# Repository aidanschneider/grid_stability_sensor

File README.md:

# grid_stability_sensor
Custom grid stability analyzer PCB.

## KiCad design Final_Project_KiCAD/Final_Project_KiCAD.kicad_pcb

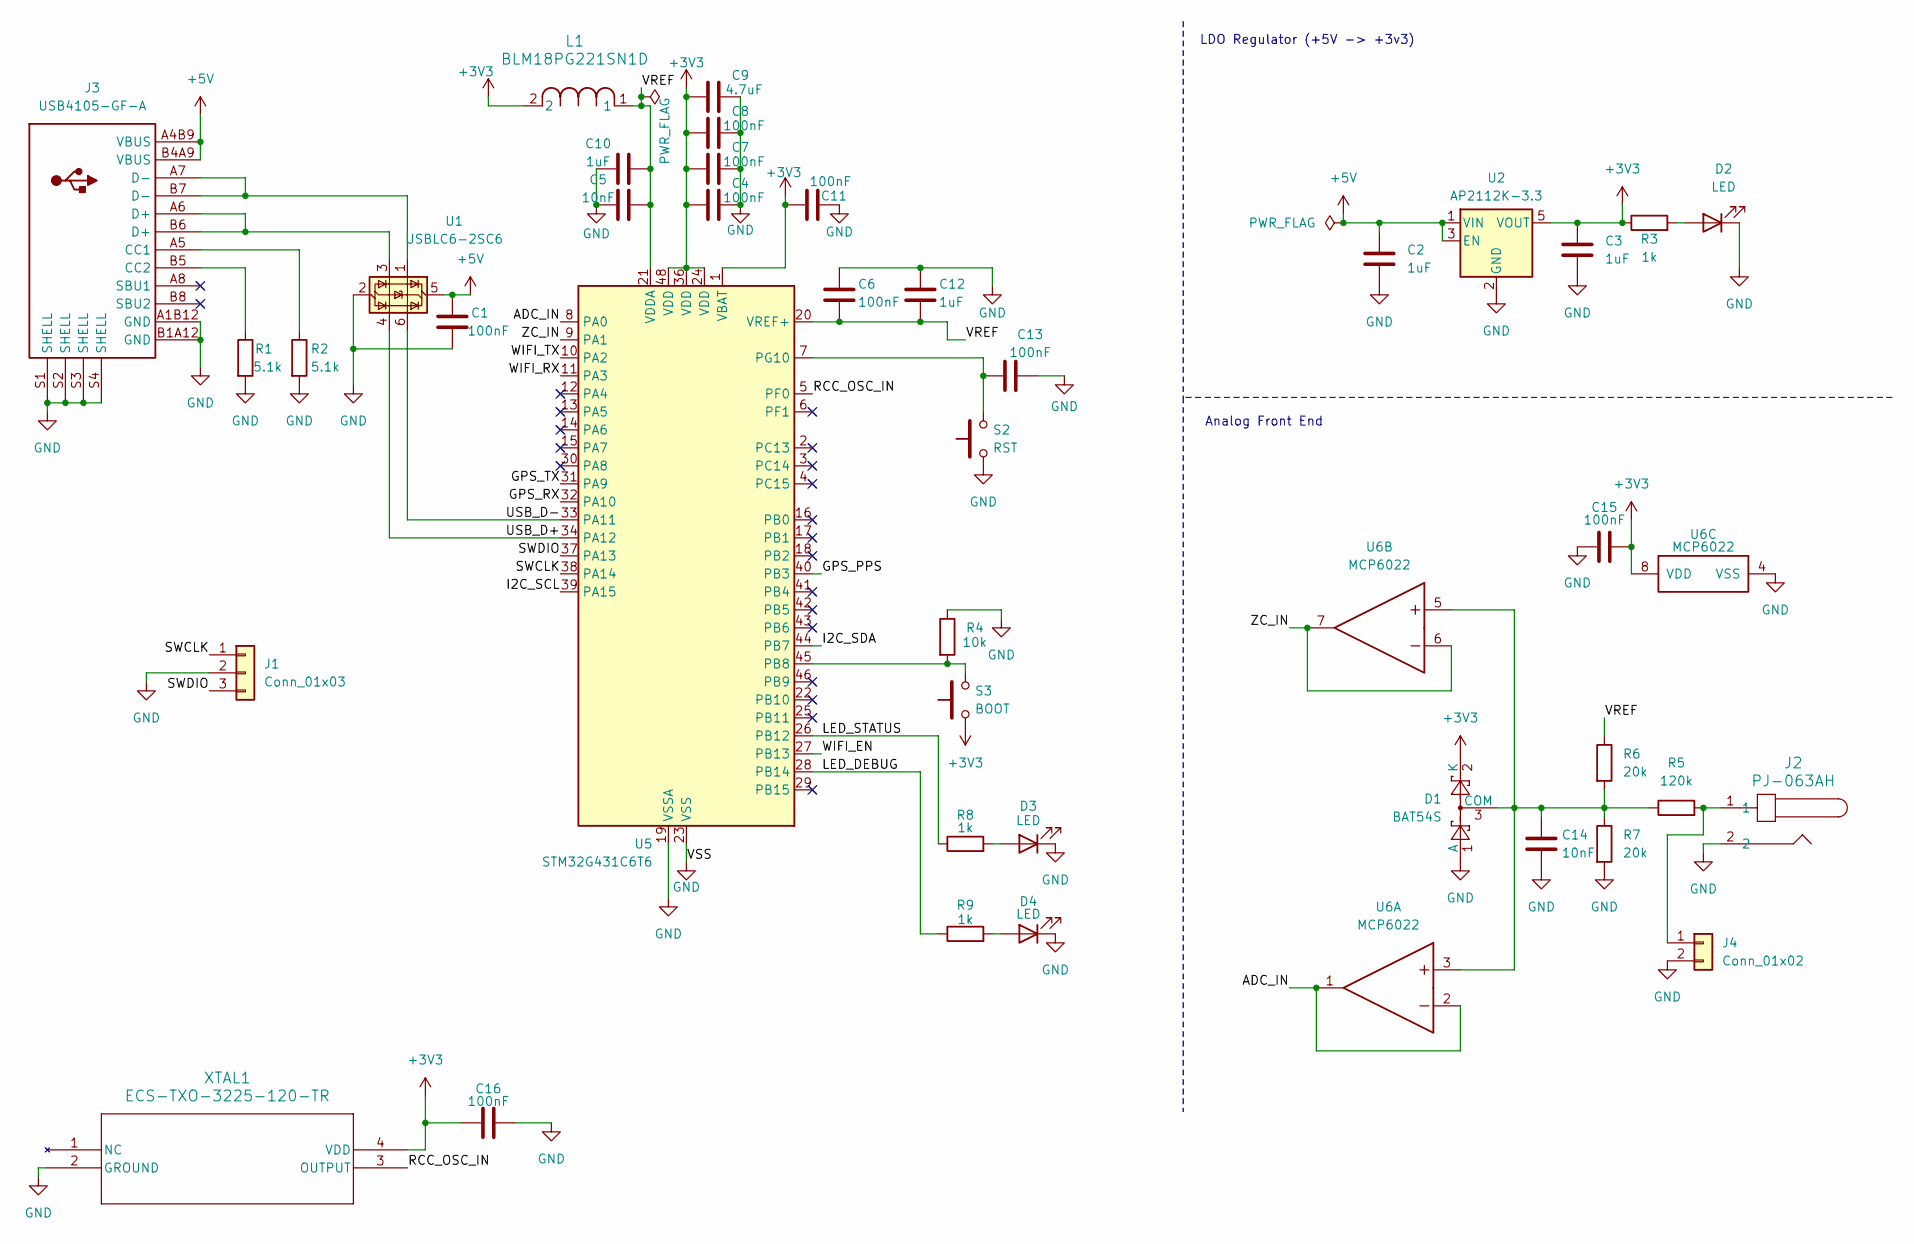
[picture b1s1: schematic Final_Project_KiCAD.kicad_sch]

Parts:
C1, C4, C6, C7, C8, C11, C13, C15, C16: 100nF; C_0603_1608Metric
C2, C3, C10, C12: 1uF; C_0603_1608Metric
C5, C14: 10nF; C_0603_1608Metric
C9: 4.7uF; C_0603_1608Metric
D1: BAT54S; SOT-23
D2, D3, D4: LED; LED_0603_1608Metric
J1: Conn_01x03; PinHeader_1x03_P2.54mm_Vertical
J2: PJ-063AH; CONN_063AH
J3: USB4105-GF-A
J4: Conn_01x02; PinHeader_1x02_P2.54mm_Vertical
L1: BLM18PG221SN1D; IND_BLM18_0603_MUR
R1, R2: 5.1k; R_0603_1608Metric
R3, R8, R9: 1k; R_0603_1608Metric
R4: 10k; R_0603_1608Metric
R5: 120k; R_0603_1608Metric
R6, R7: 20k; R_0603_1608Metric
S2: RST; SW_SPST_B3U-1000P
S3: BOOT; SW_SPST_B3U-1000P
U1: USBLC6-2SC6; SOT-23-6
U2: AP2112K-3.3; SOT-23-5
U5: STM32G431C6T6; LQFP-48_7x7mm_P0.5mm
U6: MCP6022; SOIC-8_3.9x4.9mm_P1.27mm
XTAL1: ECS-TXO-3225-120-TR; Oscillator_SMD_Abracon_ASE-4Pin_3.2x2.5mm

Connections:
+3V3: C3.1, C4.1, C7.1, C8.1, C9.1, C11.2, C15.2, C16.1, D1.2 (K), L1.2, R3.1, S3.1, U2.5 (VOUT), U5.1 (VBAT), U5.24 (VDD), U5.36 (VDD), U5.48 (VDD), U6.8 (VDD), XTAL1.4 (VDD)
+5V: C1.2, C2.1, J3.A4B9 (VBUS), J3.B4A9 (VBUS), U1.5 (VBUS), U2.1 (VIN), U2.3 (EN)
/ADC_IN: U5.8 (PA0), U6.1, U6.2
/GPS_PPS: U5.40 (PB3)
/GPS_RX: U5.32 (PA10)
/GPS_TX: U5.31 (PA9)
/I2C_SCL: U5.39 (PA15)
/I2C_SDA: U5.44 (PB7)
/LED_DEBUG: R9.1, U5.28 (PB14)
/LED_STATUS: R8.1, U5.26 (PB12)
/RCC_OSC_IN: U5.5 (PF0), XTAL1.3 (OUTPUT)
/SWCLK: J1.1, U5.38 (PA14)
/SWDIO: J1.3, U5.37 (PA13)
/USB_D+: U1.4 (I/O2), U5.34 (PA12)
/USB_D-: U1.6 (I/O1), U5.33 (PA11)
/VREF: C5.2, C6.2, C10.2, C12.2, L1.1, R6.1, U5.20 (VREF+), U5.21 (VDDA)
/WIFI_EN: U5.27 (PB13)
/WIFI_RX: U5.11 (PA3)
/WIFI_TX: U5.10 (PA2)
/ZC_IN: U5.9 (PA1), U6.6, U6.7
GND: C1.1, C2.2, C3.2, C4.2, C5.1, C6.1, C7.2, C8.2, C9.2, C10.1, C11.1, C12.1, C13.2, C14.2, C15.1, C16.2, D1.1 (A), D2.1 (K), D3.1 (K), D4.1 (K), J1.2, J2.2, J3.A1B12 (GND), J3.B1A12 (GND), J3.S1 (SHELL), J3.S2 (SHELL), J3.S3 (SHELL), J3.S4 (SHELL), J4.2, R1.2, R2.2, R4.1, R7.2, S2.1, U1.2 (GND), U2.2 (GND), U5.19 (VSSA), U5.23 (VSS), U5.35 (VSS), U5.47 (VSS), U6.4 (VSS), XTAL1.2 (GROUND)
unnamed: C14.1, D1.3 (COM), R5.1, R6.2, R7.1, U6.3, U6.5
unnamed: D2.2 (A), R3.2
unnamed: D3.2 (A), R8.2
unnamed: D4.2 (A), R9.2
unnamed: J3.A5 (CC1), R2.1
unnamed: J3.B5 (CC2), R1.1
unnamed: J3.A6 (D+), J3.B6 (D+), U1.3 (I/O2)
unnamed: J3.A7 (D-), J3.B7 (D-), U1.1 (I/O1)
unnamed: J2.1, J4.1, R5.2
unnamed: R4.2, S3.2, U5.45 (PB8)
unnamed: C13.1, S2.2, U5.7 (PG10)

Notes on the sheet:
LDO Regulator (+5V -> +3v3)
Analog Front End

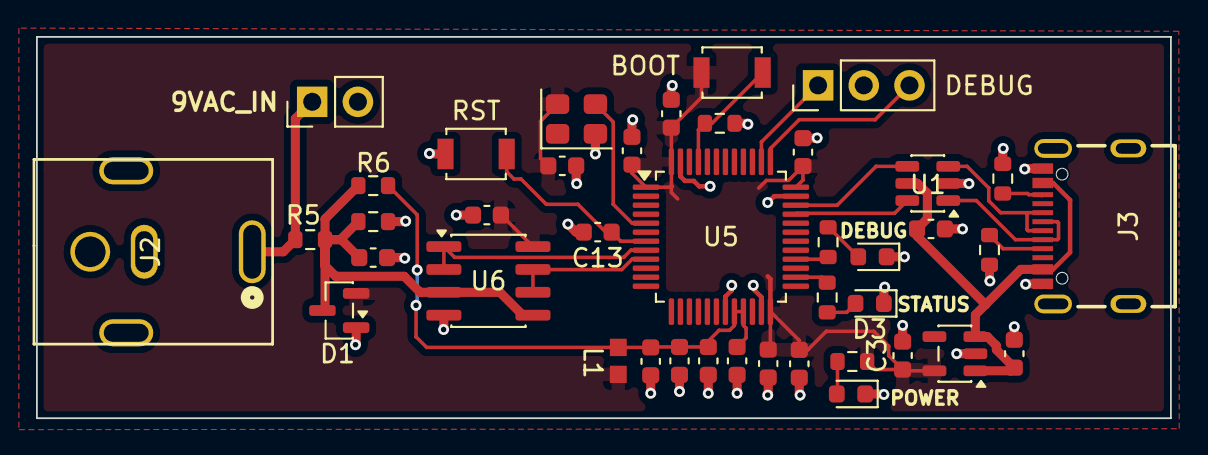
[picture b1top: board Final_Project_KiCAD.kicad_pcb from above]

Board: 2 copper layers, 63.0 x 21.2 mm, 41 parts (0 on the bottom side), 24 nets.
